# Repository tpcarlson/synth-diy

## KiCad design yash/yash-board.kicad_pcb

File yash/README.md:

# YASH

##### What is this?

A 5hp (Originally 4hp) sample and hold module, based on the schematic by [Rene Schmitz](https://www.schmitzbits.de/sah.html).

##### How much power does it use?

Basically nothing! As measured by the Joranalogue Test 3, around 10 mA on +12v and 2 mA on -12v at peak. The 5v rail is unused.

##### Where does the design come from?

This is entirely based on the [Rene Schmitz](https://www.schmitzbits.de/sah.html) YASH schematic, but with some modifications to include switches for internal/external clock. This means you can use either the internal clock, the external clock, or both which leads to some pretty interesting results.

##### Are there any rare/weird parts used?

The LF398 used is an 8-pin sample and hold chip which is the core of this whole thing and is definitely required. You'll also need a special capacitor to support this chip - see Rene's site for some more details.

##### Are there any problems with the design?

Unfortunately the first run of this ended up a little broken - the holes for the two switches were just too close to the edge and many of the PCBs ended up damaged during the de-panelling process. v2 (This version) has been increased by a couple of mm from 4hp to 5hp.

The capacitor I used does still have some droop, your mileage might vary. Definitely don't sub the S&H capacitor for a normal capacitor.

The logic PCB is also a touch longer than most of the other designs. It does fit in both the cases I have (Nifty case, and Eurorack Go), but you might want to fiddle with the design a bit to reduce the size of the logic PCB by a couple of mm.

##### Do you have a BOM/Mouser cart/Tayda links?

Sorry, no. Things go out of stock so frequently it'd be a lot of work to keep these up to date. Everything in this project is easy to source though, so you should not have any trouble.

##### Can I buy PCBs or a kit?

Send me an email (twigathy+synth@gmail.com)...

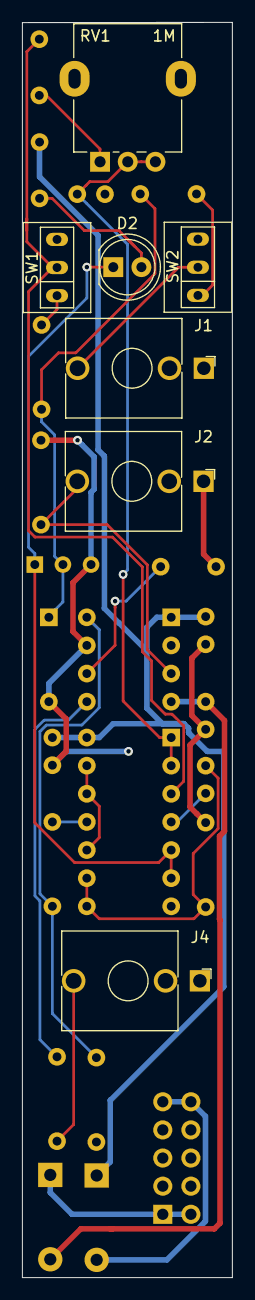
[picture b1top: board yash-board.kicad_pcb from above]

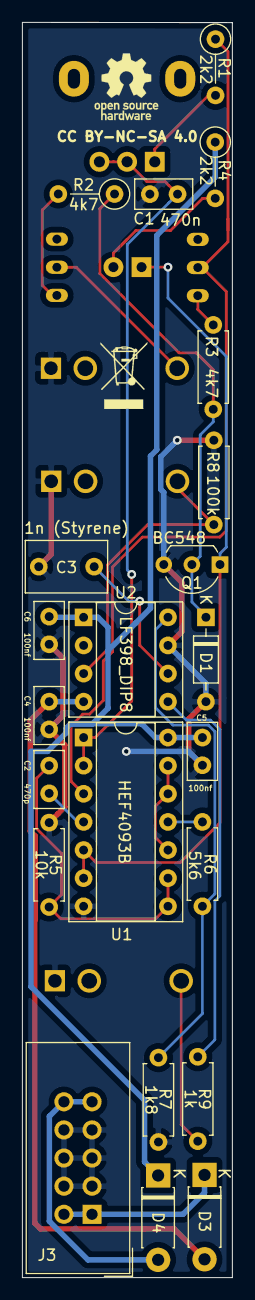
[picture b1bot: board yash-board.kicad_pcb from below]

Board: 2 copper layers, 19.0 x 113.3 mm, 31 parts (24 on the bottom side), 23 nets.

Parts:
C1: 470n; C_Disc_D5.0mm_W2.5mm_P2.50mm
C2: 470p; C_Disc_D5.0mm_W2.5mm_P2.50mm
C3: 1n (Styrene); C_Rect_L7.2mm_W4.5mm_P5.00mm_FKS2_FKP2_MKS2_MKP2
C4, C5, C6: 100nf; C_Disc_D5.0mm_W2.5mm_P2.50mm
D1: 1N4148; D_DO-35_SOD27_P7.62mm_Horizontal
D2: LED; LED_D5.0mm
D3, D4: D_Schottky; D_DO-41_SOD81_P7.62mm_Horizontal
J1, J2, J4: AudioJack2; Jack_3.5mm_QingPu_WQP-PJ398SM_Vertical_CircularHoles
J3: Conn_02x05_Odd_Even; IDC-Header_2x05_P2.54mm_Vertical
J26: WEEE; WEEE-Logo_4.2x6mm_SilkScreen
J27: OSHW; OSHW-Logo_5.7x6mm_SilkScreen
Q1: BC548; TO-92L_Inline_Wide
R1, R4: 2k2; R_Axial_DIN0207_L6.3mm_D2.5mm_P5.08mm_Vertical
R2: 4k7; R_Axial_DIN0207_L6.3mm_D2.5mm_P5.08mm_Vertical
R3: 4k7; R_Axial_DIN0207_L6.3mm_D2.5mm_P7.62mm_Horizontal
R5: 10k; R_Axial_DIN0207_L6.3mm_D2.5mm_P7.62mm_Horizontal
R6: 5k6; R_Axial_DIN0207_L6.3mm_D2.5mm_P7.62mm_Horizontal
R7: 1k8; R_Axial_DIN0207_L6.3mm_D2.5mm_P7.62mm_Horizontal
R8: 100k; R_Axial_DIN0207_L6.3mm_D2.5mm_P7.62mm_Horizontal
R9: 1k; R_Axial_DIN0207_L6.3mm_D2.5mm_P7.62mm_Horizontal
RV1: 1M; Potentiometer_Alpha_RD901F-40-00D_Single_Vertical
SW1, SW2: SW_SPDT; sub-mini-spdt-thonk
U1: HEF4093B; DIP-14_W7.62mm_Socket
U2: LF398_DIP8; DIP-8_W7.62mm_Socket

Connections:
+12V: C5.1, C6.1, D4.1, R4.1, U1.14, U2.1
-12V: C4.1, D3.2, U2.4
Earth: C1.2, C3.2, C4.2, C5.2, C6.2, D1.2, J1.S, J2.S, J3.3, J3.4, J3.5, J3.6, J3.7, J3.8, J4.S, Q1.3, R5.2, R7.2, R8.2, U1.7, U2.7
unnamed: C1.1, RV1.2, RV1.3, U1.1, U1.2
unnamed: C2.1, R5.1, U1.8, U1.9
unnamed: C2.2, U1.4
unnamed: C3.1, U2.6
unnamed: D1.1, Q1.2, R2.1, R3.1
unnamed: D2.1, Q1.1, U1.5, U1.6
unnamed: D2.2, R4.2
unnamed: D3.1, J3.1, J3.2
unnamed: D4.2, J3.9, J3.10
unnamed: J1.T, SW2.2
unnamed: J2.T, R8.1, U2.3
unnamed: J4.T, R9.1
unnamed: R1.1, SW1.2, U1.3
unnamed: R1.2, RV1.1
unnamed: R2.2, SW2.1
unnamed: R3.2, SW1.1
unnamed: R6.1, R7.1, U2.8
unnamed: R6.2, U1.11
unnamed: R9.2, U2.5
unnamed: U1.10, U1.12, U1.13

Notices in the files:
yash/yash-board.kicad_pcb:
CC BY-NC-SA 4.0
